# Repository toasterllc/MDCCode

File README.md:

## About

This repo contains all the firmware / software / Verilog for the [Photon camera](https://toaster.llc/photon).

`MDC` stands for "motion detector camera".

## Repo Organization

`Code/MSP430/MSPApp`: the MSP430 application

`Code/STM32/STMLoader`: the STM32 bootloader, which is the default application stored on the STM32's flash

`Code/STM32/STMApp`: the STM32 application, which is loaded by the Photon Transfer app when connecting the Photon camera to a Mac

`Code/ICE40/ICEAppMSP`: the top-level ICE40 Verilog that talks to `MSPApp` running on the MSP430

`Tools/MDCStudio`: the Photon Transfer Mac app

`Tools/MDCUtil`: a swiss-army utility for interacting with the Photon camera

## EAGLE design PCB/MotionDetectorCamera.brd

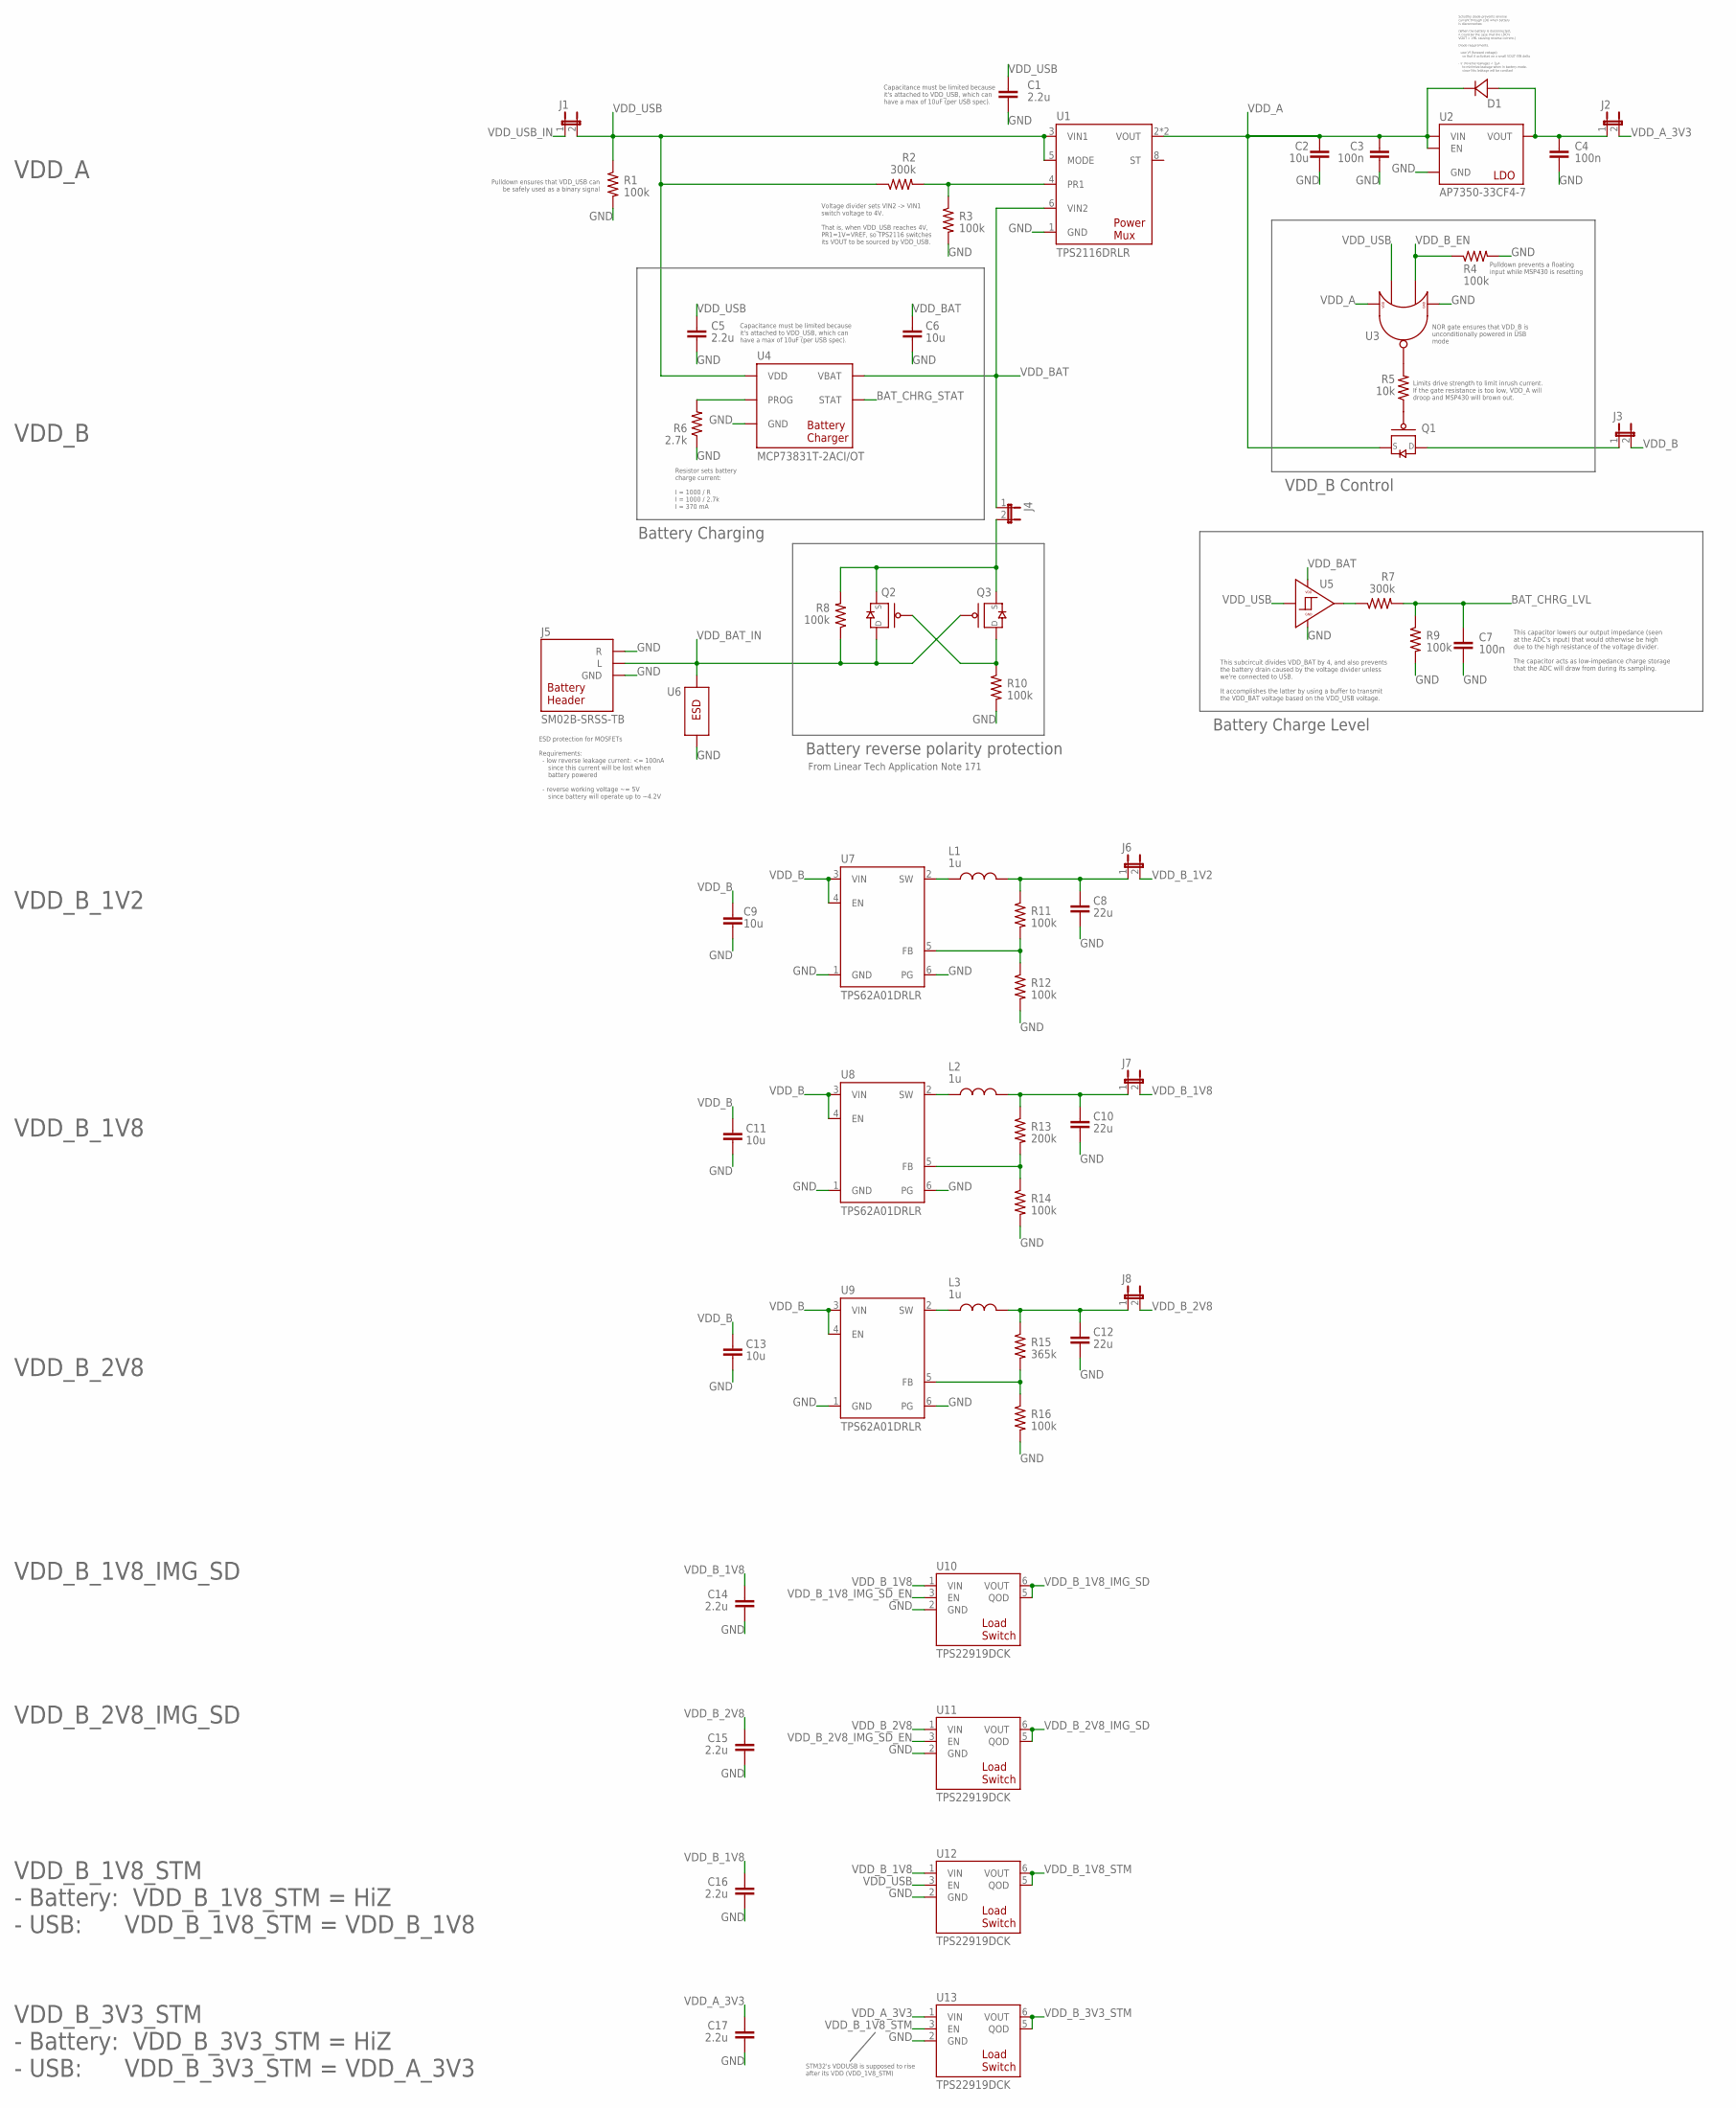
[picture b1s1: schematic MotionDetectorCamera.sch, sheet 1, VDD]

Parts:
C1, C5, C14, C15, C16, C17: 2.2u; 0402
C2, C6, C9, C11, C13: 10u; 0805
C3, C4, C7: 100n; 0402
C8, C10, C12: 22u; 0805
D1: ROHM-RB168MM-40; ROHM-SOD-123FL
J1, J2, J3, J4, J6, J7, J8: JUMPER-SOLDER
J5: JST-SM02B-SRSS-TB
L1, L2, L3: 1u; 0806
Q1, Q2, Q3: PMOS-NEXPERIA-SOT1220; NEXPERIA-SOT1220
R1, R3, R4, R8, R9, R10, R11, R12, R14, R16: 100k; 0402
R2, R7: 300k; 0402
R5: 10k; 0402
R6: 2.7k; 0402
R13: 200k; 0402
R15: 365k; 0402
U1: TI-TPS2116; TI-TPS2116DRLR
U2: DIODESINC-AP7350
U3: NEXPERIA-74LVC1G98-NOR; NEXPERIA-SOT363
U4: MICROCHIP-MCP7383X; MICROCHIP-MIC550X-SOT23-5
U5: NEXPERIA-74LVC1G98-BUFFER; NEXPERIA-SOT363
U6: EATON-STN101
U7, U8, U9: TI-TPS62A01; TI-TPS62A01DRLR
U10, U11, U12, U13: TI-TPS22919DCK

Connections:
BAT_CHRG_LVL: C7.1, R7.2, R9.1; also elsewhere on the board
BAT_CHRG_STAT: U4.1 (STAT); also elsewhere on the board
GND: C1.2, C2.2, C3.2, C4.2, C5.2, C6.2, C7.2, C8.2, C9.2, C10.2, C11.2, C12.2, C13.2, C14.2, C15.2, C16.2, C17.2, J5.GND1 (GND), J5.GND2 (GND), J5.R, R1.2, R3.2, R4.2, R6.1, R9.2, R10.2, R12.2, R14.2, R16.2, U1.1 (GND), U2.2 (GND), U3.2 (GND), U4.2 (GND), U5.2 (GND), U5.3 (GND), U6.2, U7.1 (GND), U7.6 (PG), U8.1 (GND), U8.6 (PG), U9.1 (GND), U9.6 (PG), U10.2 (GND), U11.2 (GND), U12.2 (GND), U13.2 (GND); also elsewhere on the board
unnamed: J4.2, Q2.4 (S), Q2.8 (S), Q3.4 (S), Q3.8 (S), R8.2
unnamed: C4.1, D1.1 (A), J2.1, U2.3 (VOUT)
unnamed: R7.1, U5.4 (OUT)
unnamed: Q1.3 (G), R5.1
unnamed: R5.2, U3.4 (OUT)
unnamed: C12.1, J8.1, L3.2, R15.1
unnamed: L2.1, U8.2 (SW)
unnamed: R13.2, R14.1, U8.5 (FB)
unnamed: C10.1, J7.1, L2.2, R13.1
unnamed: R6.2, U4.5 (PROG)
unnamed: L3.1, U9.2 (SW)
unnamed: L1.1, U7.2 (SW)
unnamed: Q2.3 (G), Q3.1 (D), Q3.2 (D), Q3.5 (D), Q3.6 (D), Q3.7 (D), R10.1
unnamed: R15.2, R16.1, U9.5 (FB)
unnamed: R11.2, R12.1, U7.5 (FB)
unnamed: C8.1, J6.1, L1.2, R11.1
unnamed: R2.2, R3.1, U1.4 (PR1)
unnamed: J3.1, Q1.1 (D), Q1.2 (D), Q1.5 (D), Q1.6 (D), Q1.7 (D)
VDD_A: C2.1, C3.1, D1.2 (C), Q1.4 (S), Q1.8 (S), U1.2 (VOUT), U1.7 (VOUT), U2.1 (EN), U2.4 (VIN), U3.3 (VDD), U3.5 (VDD)
VDD_A_3V3: C17.1, J2.2, U13.1 (VIN); also elsewhere on the board
VDD_B: C9.1, C11.1, C13.1, J3.2, U7.3 (VIN), U7.4 (EN), U8.3 (VIN), U8.4 (EN), U9.3 (VIN), U9.4 (EN)
VDD_BAT: C6.1, J4.1, U1.6 (VIN2), U4.3 (VBAT), U5.1 (VDD), U5.5 (VDD)
VDD_BAT_IN: J5.L, Q2.1 (D), Q2.2 (D), Q2.5 (D), Q2.6 (D), Q2.7 (D), Q3.3 (G), R8.1, U6.1
VDD_B_1V2: J6.2; also elsewhere on the board
VDD_B_1V8: C14.1, C16.1, J7.2, U10.1 (VIN), U12.1 (VIN); also elsewhere on the board
VDD_B_1V8_IMG_SD: U10.5 (QOD), U10.6 (VOUT); also elsewhere on the board
VDD_B_1V8_IMG_SD_EN: U10.3 (EN); also elsewhere on the board
VDD_B_1V8_STM: U12.5 (QOD), U12.6 (VOUT), U13.3 (EN); also elsewhere on the board
VDD_B_2V8: C15.1, J8.2, U11.1 (VIN); also elsewhere on the board
VDD_B_2V8_IMG_SD: U11.5 (QOD), U11.6 (VOUT); also elsewhere on the board
VDD_B_2V8_IMG_SD_EN: U11.3 (EN); also elsewhere on the board
VDD_B_3V3_STM: U13.5 (QOD), U13.6 (VOUT); also elsewhere on the board
VDD_B_EN: R4.1, U3.6 (IN2); also elsewhere on the board
VDD_USB: C1.1, C5.1, J1.2, R1.1, R2.1, U1.3 (VIN1), U1.5 (MODE), U3.1 (IN1), U4.4 (VDD), U5.6 (IN), U12.3 (EN)
VDD_USB_IN: J1.1; also elsewhere on the board

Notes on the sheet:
VDD_B_1V8_STM - Battery: VDD_B_1V8_STM = HiZ - USB: VDD_B_1V8_STM = VDD_B_1V8
VDD_A
VDD_B
VDD_B_1V2
VDD_B_1V8
VDD_B_2V8
VDD_B_1V8_IMG_SD
VDD_B_2V8_IMG_SD
VDD_B_3V3_STM - Battery: VDD_B_3V3_STM = HiZ - USB: VDD_B_3V3_STM = VDD_A_3V3
STM32's VDDUSB is supposed to rise after its VDD (VDD_1V8_STM)
NOR gate ensures that VDD_B is unconditionally powered in USB mode
VDD_B Control
Limits drive strength to limit inrush current. If the gate resistance is too low, VDD_A will droop and MSP430 will brown out.
From Linear Tech Application Note 171
Battery reverse polarity protection
Resistor sets battery charge current: I = 1000 / R I = 1000 / 2.7k I = 370 mA
Pulldown ensures that VDD_USB can be safely used as a binary signal
Schottky diode prevents reverse current through LDO when battery is disconnected. (When the battery is disconnected, it could be the case that the LDO's VOUT > VIN, causing reverse current.) Diode requirements: - Low Vf (forward voltage) so that it activates on a small VOUT-VIN delta - Ir (reverse 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
Voltage divider sets VIN2 -> VIN1 switch voltage to 4V. That is, when VDD_USB reaches 4V, PR1=1V=VREF, so TPS2116 switches its VOUT to be sourced by VDD_USB.
Capacitance must be limited because it's attached to VDD_USB, which can have a max of 10uF (per USB spec).
Battery Charge Level
Battery Charging
This subcircuit divides VDD_BAT by 4, and also prevents the battery drain caused by the voltage divider unless we're connected to USB. It accomplishes the latter by using a buffer to transmit the VDD_BAT voltage based on the VDD_USB voltage.
ESD protection for MOSFETs Requirements: - low reverse leakage current: <= 100nA since this current will be lost when battery powered - reverse working voltage ~= 5V since battery will operate up to ~4.2V
This capacitor lowers our output impedance (seen at the ADC's input) that would otherwise be high due to the high resistance of the voltage divider. The capacitor acts as low-impedance charge storage that the ADC will draw from during its sampling.
Pulldown prevents a floating input while MSP430 is resetting

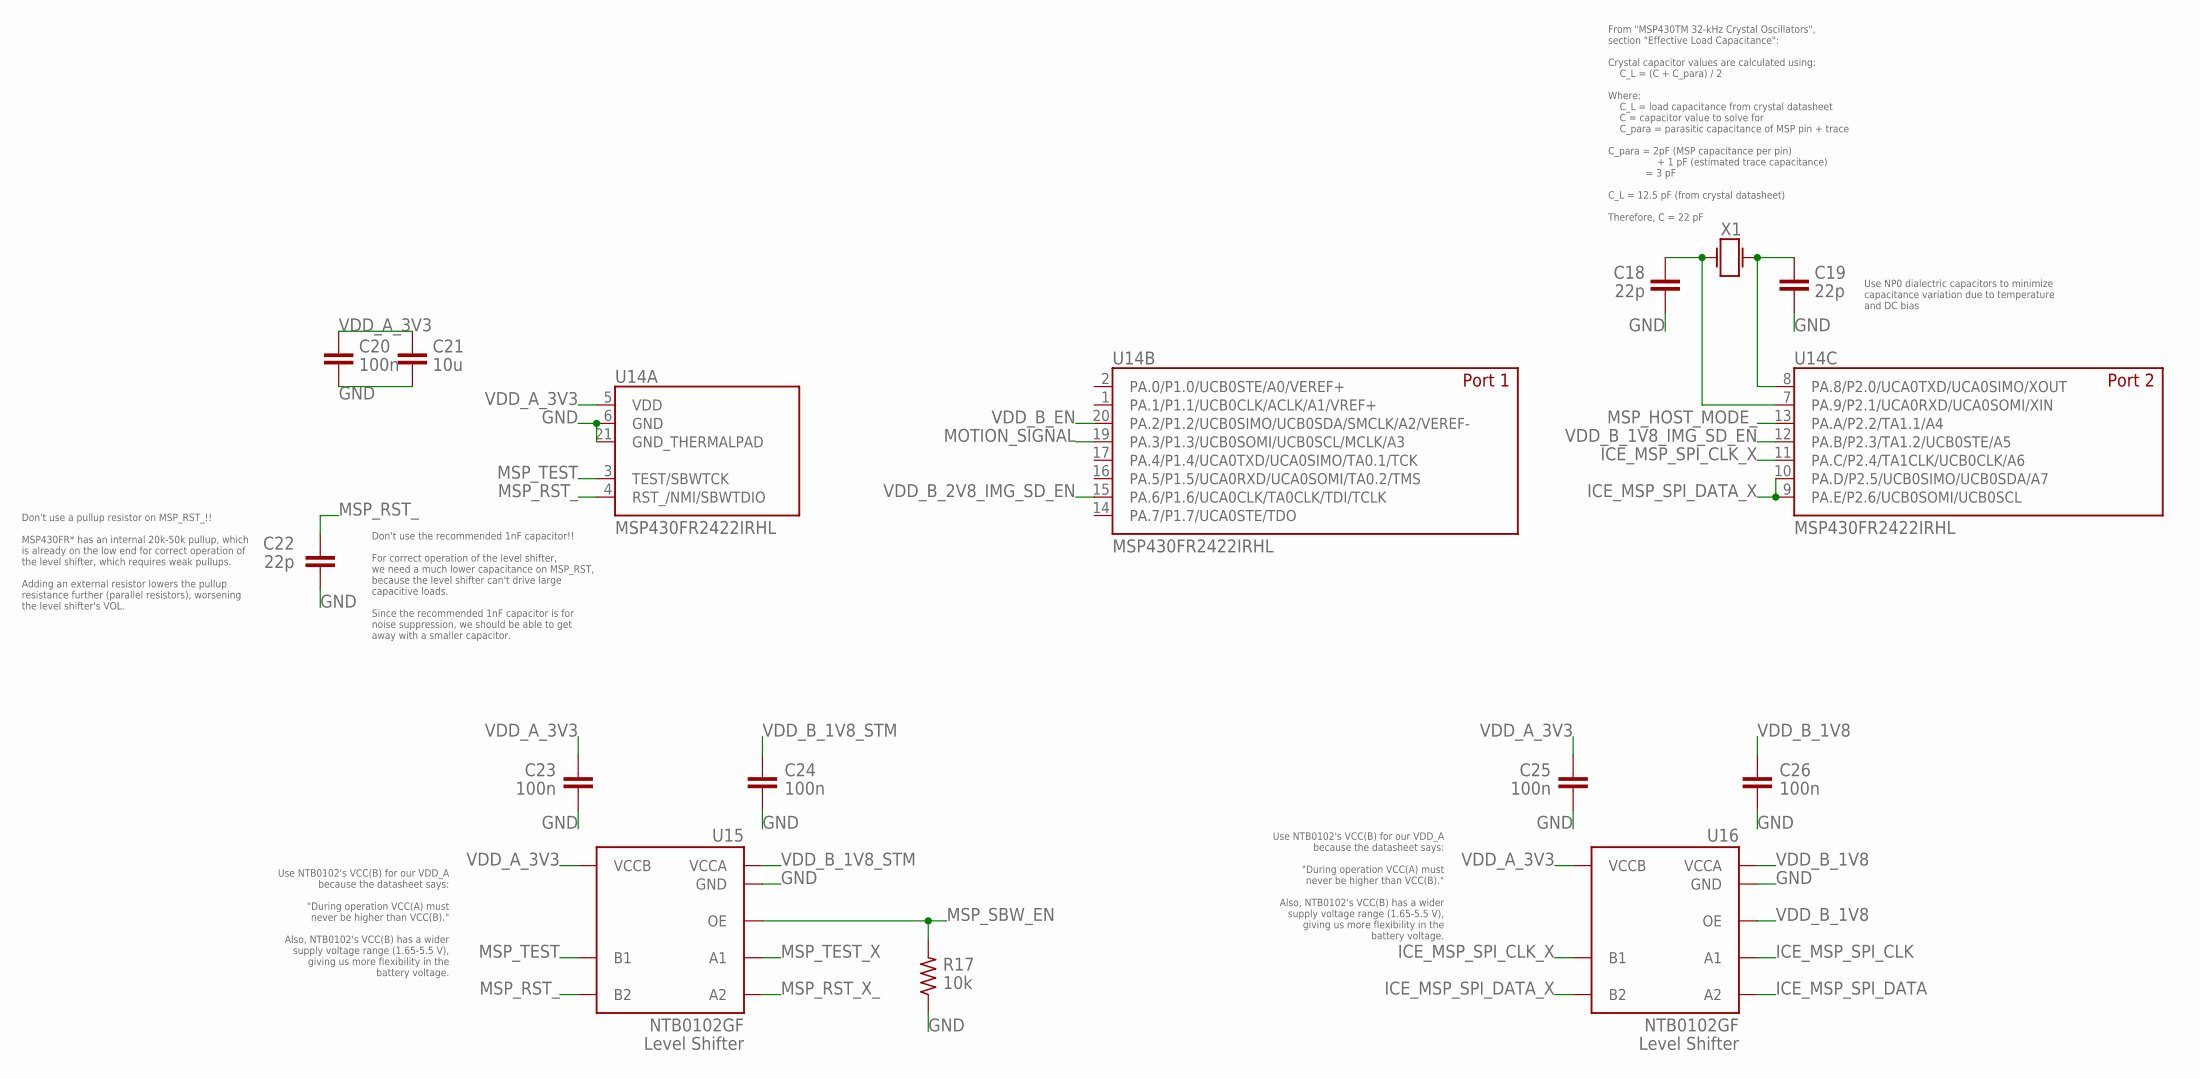
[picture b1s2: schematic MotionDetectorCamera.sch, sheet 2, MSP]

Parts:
C18, C19, C22: 22p; 0402
C20, C23, C24, C25, C26: 100n; 0402
C21: 10u; 0805
R17: 10k; 0402
U14: TI-MSP430FR2422IRHL
U15, U16: NXP-NTB0102; NXP-NTB0102GF
X1: EPSON-FC-135

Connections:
GND: C18.2, C19.2, C20.2, C21.2, C22.2, C23.2, C24.2, C25.2, C26.2, R17.1, U14.6 (GND), U14.21 (GND_THERMALPAD), U15.2 (GND), U16.2 (GND); also elsewhere on the board
ICE_MSP_SPI_CLK: U16.5 (A1); also elsewhere on the board
ICE_MSP_SPI_CLK_X: U14.11 (PA.C/P2.4/TA1CLK/UCB0CLK/A6), U16.8 (B1)
ICE_MSP_SPI_DATA: U16.4 (A2); also elsewhere on the board
ICE_MSP_SPI_DATA_X: U14.9 (PA.E/P2.6/UCB0SOMI/UCB0SCL), U14.10 (PA.D/P2.5/UCB0SIMO/UCB0SDA/A7), U16.1 (B2)
MOTION_SIGNAL: U14.19 (PA.3/P1.3/UCB0SOMI/UCB0SCL/MCLK/A3); also elsewhere on the board
MSP_HOST_MODE_: U14.13 (PA.A/P2.2/TA1.1/A4); also elsewhere on the board
MSP_RST_: C22.1, U14.4 (RST_/NMI/SBWTDIO), U15.1 (B2)
MSP_RST_X_: U15.4 (A2); also elsewhere on the board
MSP_SBW_EN: R17.2, U15.6 (OE); also elsewhere on the board
MSP_TEST: U14.3 (TEST/SBWTCK), U15.8 (B1)
MSP_TEST_X: U15.5 (A1); also elsewhere on the board
unnamed: C19.1, U14.8 (PA.8/P2.0/UCA0TXD/UCA0SIMO/XOUT), X1.2 (B)
unnamed: C18.1, U14.7 (PA.9/P2.1/UCA0RXD/UCA0SOMI/XIN), X1.1 (A)
VDD_A_3V3: C20.1, C21.1, C23.1, C25.1, U14.5 (VDD), U15.7 (VCCB), U16.7 (VCCB); also elsewhere on the board
VDD_B_1V8: C26.1, U16.3 (VCCA), U16.6 (OE); also elsewhere on the board
VDD_B_1V8_IMG_SD_EN: U14.12 (PA.B/P2.3/TA1.2/UCB0STE/A5); also elsewhere on the board
VDD_B_1V8_STM: C24.1, U15.3 (VCCA); also elsewhere on the board
VDD_B_2V8_IMG_SD_EN: U14.15 (PA.6/P1.6/UCA0CLK/TA0CLK/TDI/TCLK); also elsewhere on the board
VDD_B_EN: U14.20 (PA.2/P1.2/UCB0SIMO/UCB0SDA/SMCLK/A2/VER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); also elsewhere on the board

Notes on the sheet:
From "MSP430TM 32-kHz Crystal Oscillators", section "Effective Load Capacitance": Crystal capacitor values are calculated using: C_L = (C + C_para) / 2 Where: C_L = load capacitance from crystal datasheet C = capacitor value to solve for C_para = parasitic capacitance of MSP pin + trace C_para = 2p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
Use NP0 dialectric capacitors to minimize capacitance variation due to temperature and DC bias
Use NTB0102's VCC(B) for our VDD_A because the datasheet says: "During operation VCC(A) must never be higher than VCC(B)." Also, NTB0102's VCC(B) has a wider supply voltage range (1.65-5.5 V), giving us more flexibility in the battery voltage.
Don't use a pullup resistor on MSP_RST_!! MSP430FR* has an internal 20k-50k pullup, which is already on the low end for correct operation of the level shifter, which requires weak pullups. Adding an external resistor lowers the pullup resistance further (parallel resistors), worsening the level shi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
Don't use the recommended 1nF capacitor!! For correct operation of the level shifter, we need a much lower capacitance on MSP_RST, because the level shifter can't drive large capacitive loads. Since the recommended 1nF capacitor is for noise suppression, we should be able to get away with a smaller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

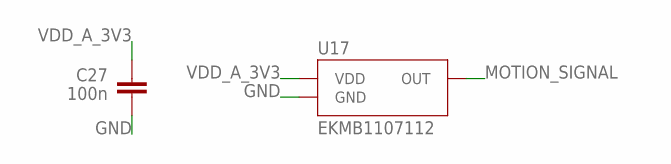
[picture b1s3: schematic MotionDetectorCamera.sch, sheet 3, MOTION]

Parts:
C27: 100n; 0402
U17: PANASONIC-EKMB110711X

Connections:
GND: C27.2, U17.3 (GND); also elsewhere on the board
MOTION_SIGNAL: U17.2 (OUT); also elsewhere on the board
VDD_A_3V3: C27.1, U17.1 (VDD); also elsewhere on the board

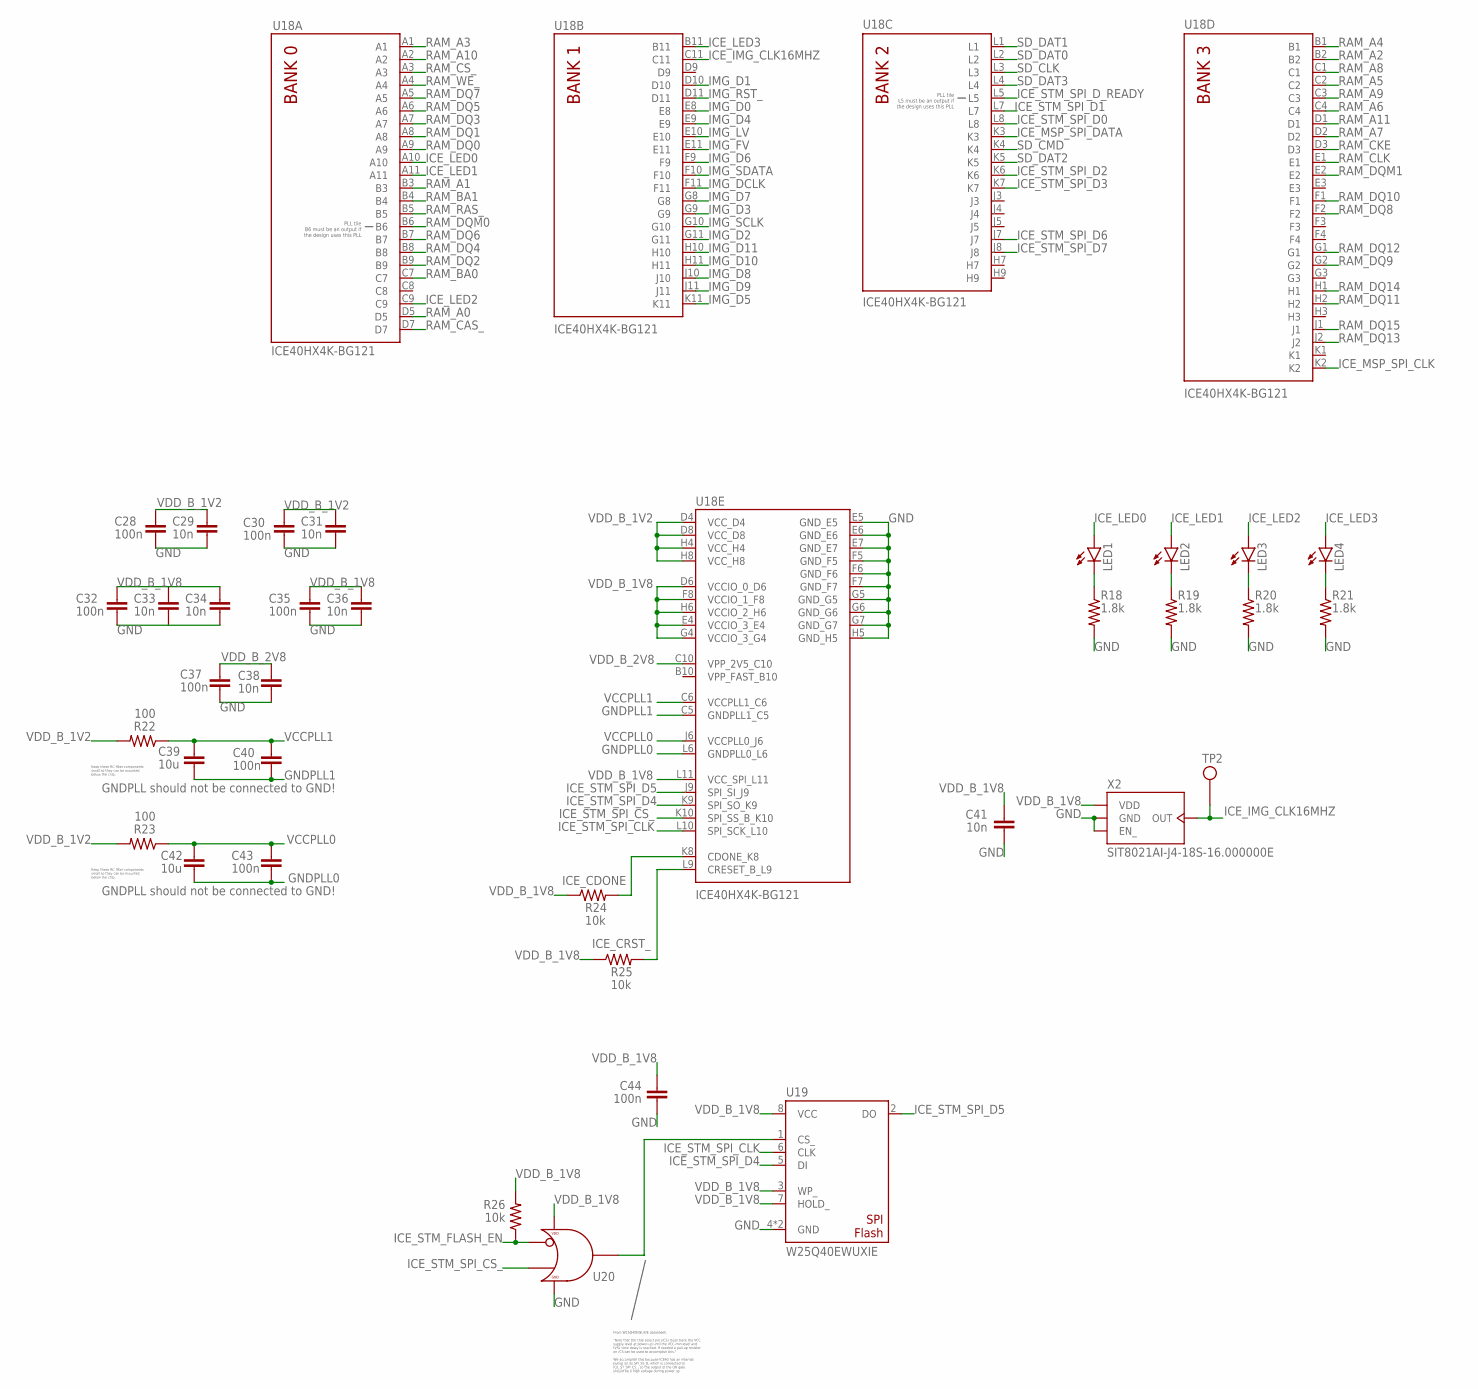
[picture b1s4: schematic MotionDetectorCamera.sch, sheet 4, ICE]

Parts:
C28, C30, C32, C35, C37, C40, C43, C44: 100n; 0402
C29, C31, C33, C34, C36, C38, C41: 10n; 0402
C39, C42: 10u; 0805
LED1, LED2, LED3, LED4: LED; LED-0603
R18, R19, R20, R21: 1.8k; 0402
R22, R23: 100; 0402
R24, R25, R26: 10k; 0402
TP2: TEST-POINT
U18: LATTICE-ICE40HX4K-BG121
U19: WINBOND-W25Q40EW; WINBOND-W25Q40EWUXIE
U20: NEXPERIA-74LVC1G98-OR-INV-INPUT; NEXPERIA-SOT363
X2: SITIME-SIT8021

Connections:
GND: C28.2, C29.2, C30.2, C31.2, C32.2, C33.2, C34.2, C35.2, C36.2, C37.2, C38.2, C41.2, C44.2, R18.2, R19.2, R20.2, R21.2, U18.E5 (GND_E5), U18.E6 (GND_E6), U18.E7 (GND_E7), U18.F5 (GND_F5), U18.F6 (GND_F6), U18.F7 (GND_F7), U18.G5 (GND_G5), U18.G6 (GND_G6), U18.G7 (GND_G7), U18.H5 (GND_H5), U19.4 (GND), U19.9 (GND), U20.2 (GND), U20.3 (GND), X2.1 (EN_), X2.4 (GND); also elsewhere on the board
GNDPLL0: C42.2, C43.2, U18.L6 (GNDPLL0_L6)
GNDPLL1: C39.2, C40.2, U18.C5 (GNDPLL1_C5)
ICE_CDONE: R24.2, U18.K8 (CDONE_K8); also elsewhere on the board
ICE_CRST_: R25.2, U18.L9 (CRESET_B_L9); also elsewhere on the board
ICE_IMG_CLK16MHZ: TP2.X, U18.C11, X2.2 (OUT); also elsewhere on the board
ICE_LED0: LED1.A, U18.A10
ICE_LED1: LED2.A, U18.A11
ICE_LED2: LED3.A, U18.C9
ICE_LED3: LED4.A, U18.B11
ICE_MSP_SPI_CLK: U18.K2; also elsewhere on the board
ICE_MSP_SPI_DATA: U18.K3; also elsewhere on the board
ICE_STM_FLASH_EN: R26.1, U20.1 (IN1); also elsewhere on the board
ICE_STM_SPI_CLK: U18.L10 (SPI_SCK_L10), U19.6 (CLK); also elsewhere on the board
ICE_STM_SPI_CS_: U18.K10 (SPI_SS_B_K10), U20.6 (IN2); also elsewhere on the board
ICE_STM_SPI_D0: U18.L8; also elsewhere on the board
ICE_STM_SPI_D1: U18.L7; also elsewhere on the board
ICE_STM_SPI_D2: U18.K6; also elsewhere on the board
ICE_STM_SPI_D3: U18.K7; also elsewhere on the board
ICE_STM_SPI_D4: U18.K9 (SPI_SO_K9), U19.5 (DI); also elsewhere on the board
ICE_STM_SPI_D5: U18.J9 (SPI_SI_J9), U19.2 (DO); also elsewhere on the board
ICE_STM_SPI_D6: U18.J7; also elsewhere on the board
ICE_STM_SPI_D7: U18.J8; also elsewhere on the board
ICE_STM_SPI_D_READY: U18.L5; also elsewhere on the board
IMG_D0: U18.E8; also elsewhere on the board
IMG_D1: U18.D10; also elsewhere on the board
IMG_D2: U18.G11; also elsewhere on the board
IMG_D3: U18.G9; also elsewhere on the board
IMG_D4: U18.E9; also elsewhere on the board
IMG_D5: U18.K11; also elsewhere on the board
IMG_D6: U18.F9; also elsewhere on the board
IMG_D7: U18.G8; also elsewhere on the board
IMG_D8: U18.J10; also elsewhere on the board
IMG_D9: U18.J11; also elsewhere on the board
IMG_D10: U18.H11; also elsewhere on the board
IMG_D11: U18.H10; also elsewhere on the board
IMG_DCLK: U18.F11; also elsewhere on the board
IMG_FV: U18.E11; also elsewhere on the board
IMG_LV: U18.E10; also elsewhere on the board
IMG_RST_: U18.D11; also elsewhere on the board
IMG_SCLK: U18.G10; also elsewhere on the board
IMG_SDATA: U18.F10; also elsewhere on the board
unnamed: LED1.C, R18.1
unnamed: LED3.C, R20.1
unnamed: LED2.C, R19.1
unnamed: LED4.C, R21.1
unnamed: U19.1 (CS_), U20.4 (OUT)
RAM_A0: U18.D5; also elsewhere on the board
RAM_A1: U18.B3; also elsewhere on the board
RAM_A2: U18.B2; also elsewhere on the board
RAM_A3: U18.A1; also elsewhere on the board
RAM_A4: U18.B1; also elsewhere on the board
RAM_A5: U18.C2; also elsewhere on the board
RAM_A6: U18.C4; also elsewhere on the board
RAM_A7: U18.D2; also elsewhere on the board
RAM_A8: U18.C1; also elsewhere on the board
RAM_A9: U18.C3; also elsewhere on the board
RAM_A10: U18.A2; also elsewhere on the board
RAM_A11: U18.D1; also elsewhere on the board
RAM_BA0: U18.C7; also elsewhere on the board
RAM_BA1: U18.B4; also elsewhere on the board
RAM_CAS_: U18.D7; also elsewhere on the board
RAM_CKE: U18.D3; also elsewhere on the board
RAM_CLK: U18.E1; also elsewhere on the board
RAM_CS_: U18.A3; also elsewhere on the board
RAM_DQ0: U18.A9; also elsewhere on the board
RAM_DQ1: U18.A8; also elsewhere on the board
RAM_DQ2: U18.B9; also elsewhere on the board
RAM_DQ3: U18.A7; also elsewhere on the board
RAM_DQ4: U18.B8; also elsewhere on the board
RAM_DQ5: U18.A6; also elsewhere on the board
RAM_DQ6: U18.B7; also elsewhere on the board
RAM_DQ7: U18.A5; also elsewhere on the board
RAM_DQ8: U18.F2; also elsewhere on the board
RAM_DQ9: U18.G2; also elsewhere on the board
RAM_DQ10: U18.F1; also elsewhere on the board
RAM_DQ11: U18.H2; also elsewhere on the board
RAM_DQ12: U18.G1; also elsewhere on the board
RAM_DQ13: U18.J2; also elsewhere on the board
RAM_DQ14: U18.H1; also elsewhere on the board
RAM_DQ15: U18.J1; also elsewhere on the board
RAM_DQM0: U18.B6; also elsewhere on the board
RAM_DQM1: U18.E2; also elsewhere on the board
RAM_RAS_: U18.B5; also elsewhere on the board
RAM_WE_: U18.A4; also elsewhere on the board
SD_CLK: U18.L3; also elsewhere on the board
SD_CMD: U18.K4; also elsewhere on the board
SD_DAT0: U18.L2; also elsewhere on the board
SD_DAT1: U18.L1; also elsewhere on the board
SD_DAT2: U18.K5; also elsewhere on the board
SD_DAT3: U18.L4; also elsewhere on the board
VCCPLL0: C42.1, C43.1, R23.1, U18.J6 (VCCPLL0_J6)
VCCPLL1: C39.1, C40.1, R22.1, U18.C6 (VCCPLL1_C6)
VDD_B_1V2: C28.1, C29.1, C30.1, C31.1, R22.2, R23.2, U18.D4 (VCC_D4), U18.D8 (VCC_D8), U18.H4 (VCC_H4), U18.H8 (VCC_H8); also elsewhere on the board
VDD_B_1V8: C32.1, C33.1, C34.1, C35.1, C36.1, C41.1, C44.1, R24.1, R25.1, R26.2, U18.D6 (VCCIO_0_D6), U18.E4 (VCCIO_3_E4), U18.F8 (VCCIO_1_F8), U18.G4 (VCCIO_3_G4), U18.H6 (VCCIO_2_H6), U18.L11 (VCC_SPI_L11), U19.3 (WP_), U19.7 (HOLD_), U19.8 (VCC), U20.5 (VDD), X2.3 (VDD); also elsewhere on the board
VDD_B_2V8: C37.1, C38.1, U18.C10 (VPP_2V5_C10); also elsewhere on the board

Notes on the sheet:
GNDPLL should not be connected to GND!
Keep these RC filter components small so they can be mounted below the chip.
From W25Q40EWUXIE datasheet: "Note that the chip select pin (/CS) must track the VCC supply level at power-up until the VCC-min level and tVSL time delay is reached. If needed a pull-up resister on /CS can be used to accomplish this." We accomplish this because ICE40 has an internal pullup on its S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

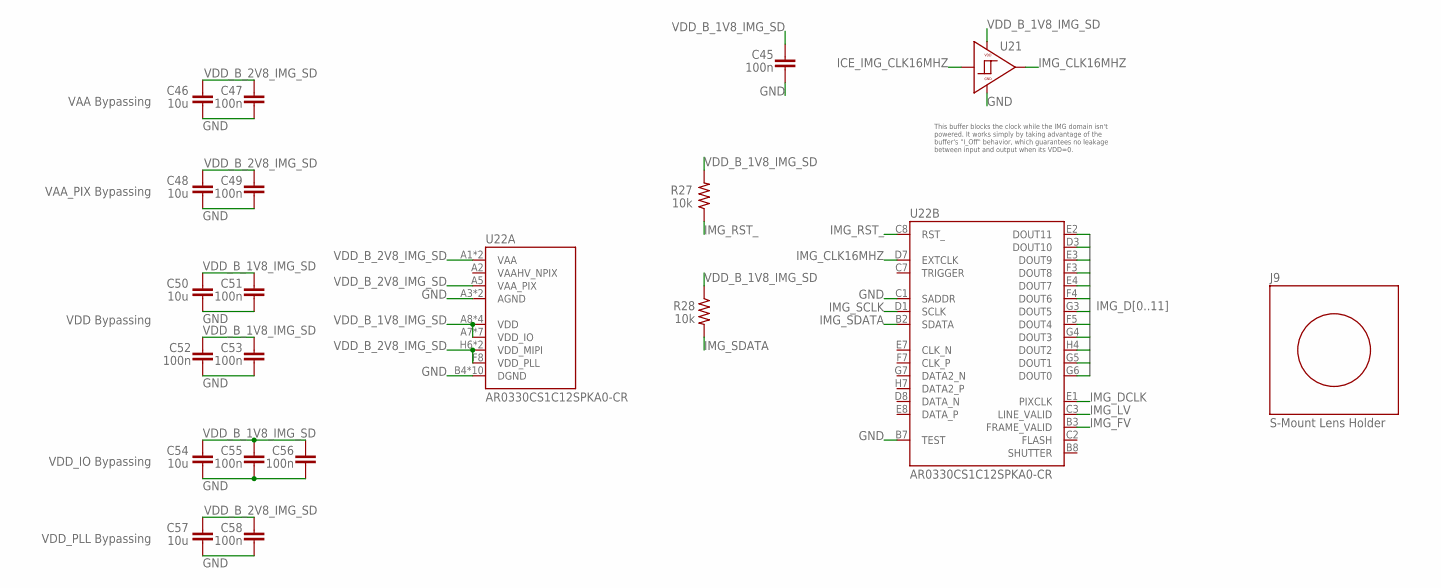
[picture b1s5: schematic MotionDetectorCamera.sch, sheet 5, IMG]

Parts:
C45, C47, C49, C51, C52, C53, C55, C56, C58: 100n; 0402
C46, C48, C50, C54, C57: 10u; 0805
J9: S-MOUNT-LENS-HOLDERM12LENSES-PT-LH008P; M12LENSES-PT-LH008P
R27, R28: 10k; 0402
U21: NEXPERIA-74LVC1G98-BUFFER; NEXPERIA-SOT363
U22: ON-AR0330CS1C12SPKA0

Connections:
GND: C45.2, C46.2, C47.2, C48.2, C49.2, C50.2, C51.2, C52.2, C53.2, C54.2, C55.2, C56.2, C57.2, C58.2, U21.2 (GND), U21.3 (GND), U22.A3 (AGND), U22.B4 (DGND), U22.B5 (AGND), U22.B6 (DGND), U22.B7 (TEST), U22.C1 (SADDR), U22.C4 (DGND), U22.C5 (DGND), U22.C6 (DGND), U22.D4 (DGND), U22.E6 (DGND), U22.G1 (DGND), U22.H2 (DGND), U22.H3 (DGND); also elsewhere on the board
ICE_IMG_CLK16MHZ: U21.6 (IN); also elsewhere on the board
IMG_CLK16MHZ: U21.4 (OUT), U22.D7 (EXTCLK)
IMG_D0: U22.G6 (DOUT0); also elsewhere on the board
IMG_D1: U22.G5 (DOUT1); also elsewhere on the board
IMG_D2: U22.H4 (DOUT2); also elsewhere on the board
IMG_D3: U22.G4 (DOUT3); also elsewhere on the board
IMG_D4: U22.F5 (DOUT4); also elsewhere on the board
IMG_D5: U22.G3 (DOUT5); also elsewhere on the board
IMG_D6: U22.F4 (DOUT6); also elsewhere on the board
IMG_D7: U22.E4 (DOUT7); also elsewhere on the board
IMG_D8: U22.F3 (DOUT8); also elsewhere on the board
IMG_D9: U22.E3 (DOUT9); also elsewhere on the board
IMG_D10: U22.D3 (DOUT10); also elsewhere on the board
IMG_D11: U22.E2 (DOUT11); also elsewhere on the board
IMG_DCLK: U22.E1 (PIXCLK); also elsewhere on the board
IMG_FV: U22.B3 (FRAME_VALID); also elsewhere on the board
IMG_LV: U22.C3 (LINE_VALID); also elsewhere on the board
IMG_RST_: R27.1, U22.C8 (RST_); also elsewhere on the board
IMG_SCLK: U22.D1 (SCLK); also elsewhere on the board
IMG_SDATA: R28.2, U22.B2 (SDATA); also elsewhere on the board
VDD_B_1V8_IMG_SD: C45.1, C50.1, C51.1, C52.1, C53.1, C54.1, C55.1, C56.1, R27.2, R28.1, U21.1 (VDD), U21.5 (VDD), U22.A7 (VDD_IO), U22.A8 (VDD), U22.B1 (VDD), U22.D2 (VDD_IO), U22.D5 (VDD_IO), U22.D6 (VDD_IO), U22.E5 (VDD_IO), U22.F6 (VDD_IO), U22.G2 (VDD), U22.G8 (VDD), U22.H5 (VDD_IO); also elsewhere on the board
VDD_B_2V8_IMG_SD: C46.1, C47.1, C48.1, C49.1, C57.1, C58.1, U22.A1 (VAA), U22.A5 (VAA_PIX), U22.A6 (VAA), U22.F8 (VDD_PLL), U22.H6 (VDD_MIPI), U22.H8 (VDD_MIPI); also elsewhere on the board

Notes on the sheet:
VAA Bypassing
VAA_PIX Bypassing
VDD Bypassing
VDD_IO Bypassing
VDD_PLL Bypassing
This buffer blocks the clock while the IMG domain isn't powered. It works simply by taking advantage of the buffer's "I_Off" behavior, which guarantees no leakage between input and output when its VDD=0.

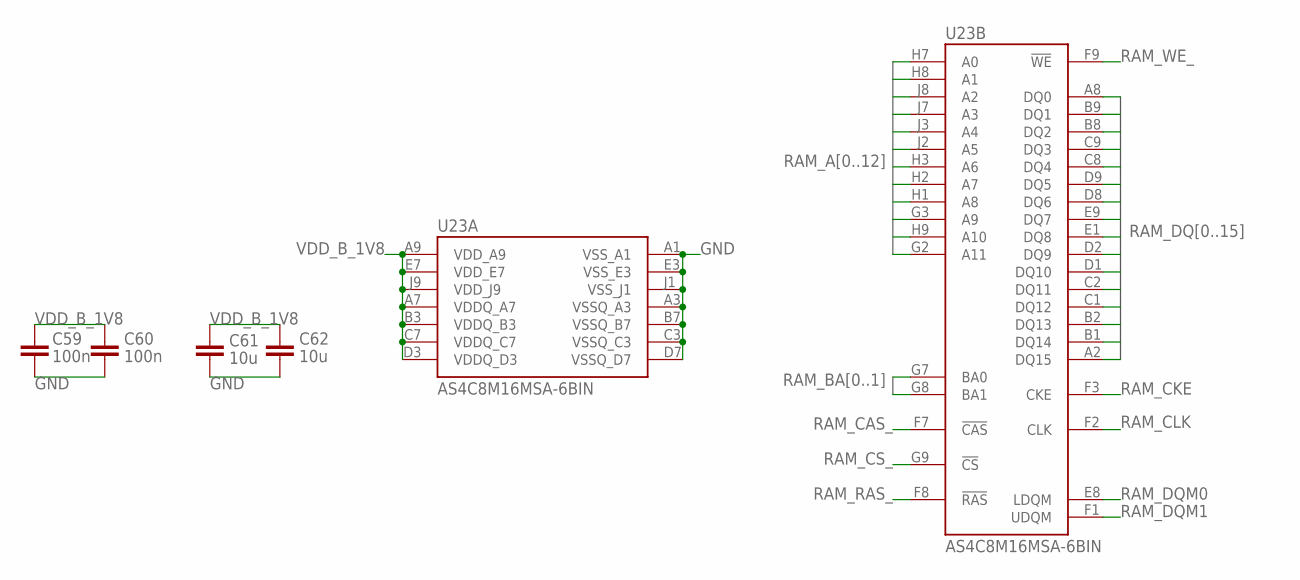
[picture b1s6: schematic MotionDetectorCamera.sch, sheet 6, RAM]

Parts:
C59, C60: 100n; 0402
C61, C62: 10u; 0805
U23: ALLIANCE-AS4C8M16MSA-6BIN

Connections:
GND: C59.2, C60.2, C61.2, C62.2, U23.A1 (VSS_A1), U23.A3 (VSSQ_A3), U23.B7 (VSSQ_B7), U23.C3 (VSSQ_C3), U23.D7 (VSSQ_D7), U23.E3 (VSS_E3), U23.J1 (VSS_J1); also elsewhere on the board
RAM_A0: U23.H7 (A0); also elsewhere on the board
RAM_A1: U23.H8 (A1); also elsewhere on the board
RAM_A2: U23.J8 (A2); also elsewhere on the board
RAM_A3: U23.J7 (A3); also elsewhere on the board
RAM_A4: U23.J3 (A4); also elsewhere on the board
RAM_A5: U23.J2 (A5); also elsewhere on the board
RAM_A6: U23.H3 (A6); also elsewhere on the board
RAM_A7: U23.H2 (A7); also elsewhere on the board
RAM_A8: U23.H1 (A8); also elsewhere on the board
RAM_A9: U23.G3 (A9); also elsewhere on the board
RAM_A10: U23.H9 (A10); also elsewhere on the board
RAM_A11: U23.G2 (A11); also elsewhere on the board
RAM_BA0: U23.G7 (BA0); also elsewhere on the board
RAM_BA1: U23.G8 (BA1); also elsewhere on the board
RAM_CAS_: U23.F7 (!CAS!); also elsewhere on the board
RAM_CKE: U23.F3 (CKE); also elsewhere on the board
RAM_CLK: U23.F2 (CLK); also elsewhere on the board
RAM_CS_: U23.G9 (!CS!); also elsewhere on the board
RAM_DQ0: U23.A8 (DQ0); also elsewhere on the board
RAM_DQ1: U23.B9 (DQ1); also elsewhere on the board
RAM_DQ2: U23.B8 (DQ2); also elsewhere on the board
RAM_DQ3: U23.C9 (DQ3); also elsewhere on the board
RAM_DQ4: U23.C8 (DQ4); also elsewhere on the board
RAM_DQ5: U23.D9 (DQ5); also elsewhere on the board
RAM_DQ6: U23.D8 (DQ6); also elsewhere on the board
RAM_DQ7: U23.E9 (DQ7); also elsewhere on the board
RAM_DQ8: U23.E1 (DQ8); also elsewhere on the board
RAM_DQ9: U23.D2 (DQ9); also elsewhere on the board
RAM_DQ10: U23.D1 (DQ10); also elsewhere on the board
RAM_DQ11: U23.C2 (DQ11); also elsewhere on the board
RAM_DQ12: U23.C1 (DQ12); also elsewhere on the board
RAM_DQ13: U23.B2 (DQ13); also elsewhere on the board
RAM_DQ14: U23.B1 (DQ14); also elsewhere on the board
RAM_DQ15: U23.A2 (DQ15); also elsewhere on the board
RAM_DQM0: U23.E8 (LDQM); also elsewhere on the board
RAM_DQM1: U23.F1 (UDQM); also elsewhere on the board
RAM_RAS_: U23.F8 (!RAS!); also elsewhere on the board
RAM_WE_: U23.F9 (!WE!); also elsewhere on the board
VDD_B_1V8: C59.1, C60.1, C61.1, C62.1, U23.A7 (VDDQ_A7), U23.A9 (VDD_A9), U23.B3 (VDDQ_B3), U23.C7 (VDDQ_C7), U23.D3 (VDDQ_D3), U23.E7 (VDD_E7), U23.J9 (VDD_J9); also elsewhere on the board

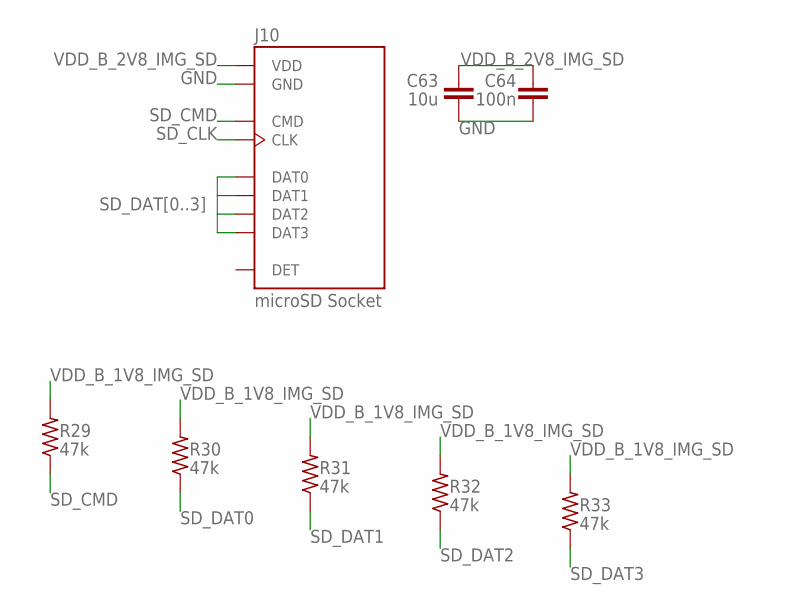
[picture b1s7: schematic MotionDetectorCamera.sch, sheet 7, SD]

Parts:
C63: 10u; 0805
C64: 100n; 0402
J10: MICROSD-SOCKET; MOLEX-1051620001
R29, R30, R31, R32, R33: 47k; 0402

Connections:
GND: C63.2, C64.2, J10.GND1 (GND), J10.GND2 (GND), J10.GND3 (GND), J10.GND4 (GND), J10.VSS (GND); also elsewhere on the board
SD_CLK: J10.CLK; also elsewhere on the board
SD_CMD: J10.CMD, R29.1; also elsewhere on the board
SD_DAT0: J10.DAT0, R30.1; also elsewhere on the board
SD_DAT1: J10.DAT1, R31.1; also elsewhere on the board
SD_DAT2: J10.DAT2, R32.1; also elsewhere on the board
SD_DAT3: J10.DAT3, R33.1; also elsewhere on the board
VDD_B_1V8_IMG_SD: R29.2, R30.2, R31.2, R32.2, R33.2; also elsewhere on the board
VDD_B_2V8_IMG_SD: C63.1, C64.1, J10.VDD; also elsewhere on the board
